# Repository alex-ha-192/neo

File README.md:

# Neo
 
The Neo buzzer system is an open-source, hopefully reliable, and hopefully affordable line of quiz lockout buzzers. It also does not currently exist. This is a rather significant flaw, though one I'm working to repair.

The initial planning is for one set of buzzers intended to have user-facing backwards compatibility with a popular set of commercial buzzers. A cheaper option may follow depending on how that goes.

## Progress

### Classic v1

- [x] Finalise design concepts
- [x] Source parts
- [ ] PCB design
- [ ] Order and initial testing
- [ ] 3D printed case design
- [ ] Real-world testing
- [ ] Release

## Pricing

I'm trying to be cost-conscious while designing these buzzers, but I'm not planning on imminently selling any or distributing them beyond Imperial until they're both finished and well-tested. If you need a buzzer set now, I'll point you to buying a [Kitsune system](https://github.com/Amekyras/kitsune) from [Aisling Skeet](https://github.com/Amekyras); they're a solid set of buzzers and they've been tested at quite a few competitive events. If you want a pricing estimate, it's probably whatever I say it is at the moment plus a bit on top because this keeps getting more expensive with every revision.

Just a quick note as well, this is an open-source project and, as a result, you can do whatever you'd like as per the [licence](LICENCE), but if you want to make your own buzzers, please don't sell them? Obviously I neither can nor will try and stop you, but these haven't been particularly cheap to work on, even though as I write this I haven't shipped out any PCBs yet - parts are expensive! I'd love it if anyone who wants to improve them does that though, either on this repository or on your own fork.

## Features (planned, WIP)

### Classic v1.0

- Daisy-chain as many buzzers per side as you could ever reasonably want
- USB-C connection with data for potential [BuzzIn.live](https://buzzin.live) support or generic input
- Low/fair latency
- Static discharge protection and industrial signalling for reliability
- At-home reflashable central unit firmware for customisation/DIY firmware upgrades
- Open source!

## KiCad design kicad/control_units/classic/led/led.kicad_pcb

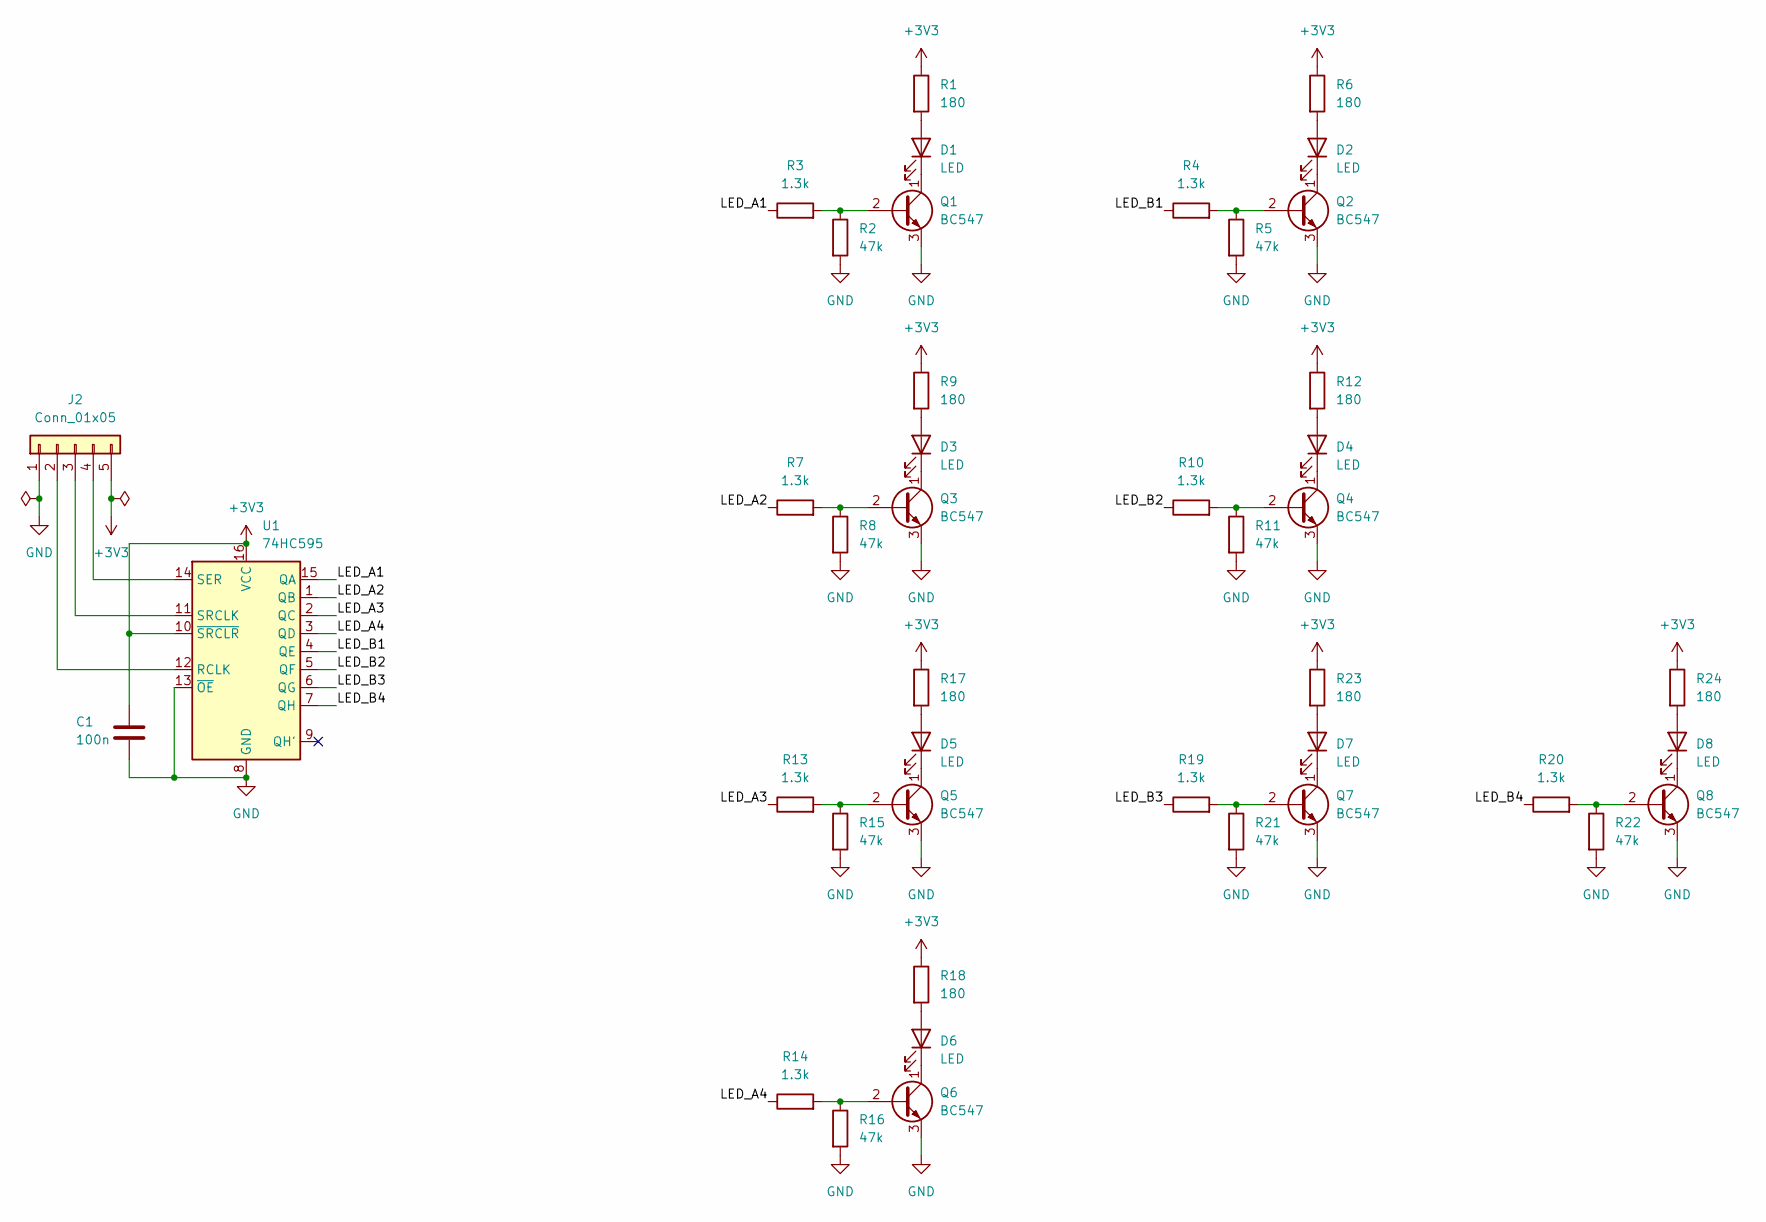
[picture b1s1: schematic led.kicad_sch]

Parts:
C1: 100n; C_Disc_D5.0mm_W2.5mm_P2.50mm
D1, D2, D3, D4, D5, D6, D7, D8: LED; LED_D5.0mm
J2: Conn_01x05; PinSocket_1x05_P2.54mm_Vertical
Q1, Q2, Q3, Q4, Q5, Q6, Q7, Q8: BC547; TO-92_Inline
R1, R6, R9, R12, R17, R18, R23, R24: 180; R_Axial_DIN0207_L6.3mm_D2.5mm_P7.62mm_Horizontal
R2, R5, R8, R11, R15, R16, R21, R22: 47k; R_Axial_DIN0207_L6.3mm_D2.5mm_P7.62mm_Horizontal
R3, R4, R7, R10, R13, R14, R19, R20: 1.3k; R_Axial_DIN0207_L6.3mm_D2.5mm_P7.62mm_Horizontal
U1: 74HC595; DIP-16_W7.62mm

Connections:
+3V3: C1.1, J2.5, R1.1, R6.1, R9.1, R12.1, R17.1, R18.1, R23.1, R24.1, U1.10 (~SRCLR), U1.16 (VCC)
/LED_A1: R3.1, U1.15 (QA)
/LED_A2: R7.1, U1.1 (QB)
/LED_A3: R13.1, U1.2 (QC)
/LED_A4: R14.1, U1.3 (QD)
/LED_B1: R4.1, U1.4 (QE)
/LED_B2: R10.1, U1.5 (QF)
/LED_B3: R19.1, U1.6 (QG)
/LED_B4: R20.1, U1.7 (QH)
GND: C1.2, J2.1, Q1.3 (E), Q2.3 (E), Q3.3 (E), Q4.3 (E), Q5.3 (E), Q6.3 (E), Q7.3 (E), Q8.3 (E), R2.2, R5.2, R8.2, R11.2, R15.2, R16.2, R21.2, R22.2, U1.8 (GND), U1.13 (~OE)
unnamed: D1.2 (A), R1.2
unnamed: D1.1 (K), Q1.1 (C)
unnamed: D2.2 (A), R6.2
unnamed: D2.1 (K), Q2.1 (C)
unnamed: D3.2 (A), R9.2
unnamed: D3.1 (K), Q3.1 (C)
unnamed: D4.2 (A), R12.2
unnamed: D4.1 (K), Q4.1 (C)
unnamed: D5.2 (A), R17.2
unnamed: D5.1 (K), Q5.1 (C)
unnamed: D6.2 (A), R18.2
unnamed: D6.1 (K), Q6.1 (C)
unnamed: D7.2 (A), R23.2
unnamed: D7.1 (K), Q7.1 (C)
unnamed: D8.2 (A), R24.2
unnamed: D8.1 (K), Q8.1 (C)
unnamed: J2.2, U1.12 (RCLK)
unnamed: J2.3, U1.11 (SRCLK)
unnamed: J2.4, U1.14 (SER)
unnamed: Q1.2 (B), R2.1, R3.2
unnamed: Q2.2 (B), R4.2, R5.1
unnamed: Q3.2 (B), R7.2, R8.1
unnamed: Q4.2 (B), R10.2, R11.1
unnamed: Q5.2 (B), R13.2, R15.1
unnamed: Q6.2 (B), R14.2, R16.1
unnamed: Q7.2 (B), R19.2, R21.1
unnamed: Q8.2 (B), R20.2, R22.1

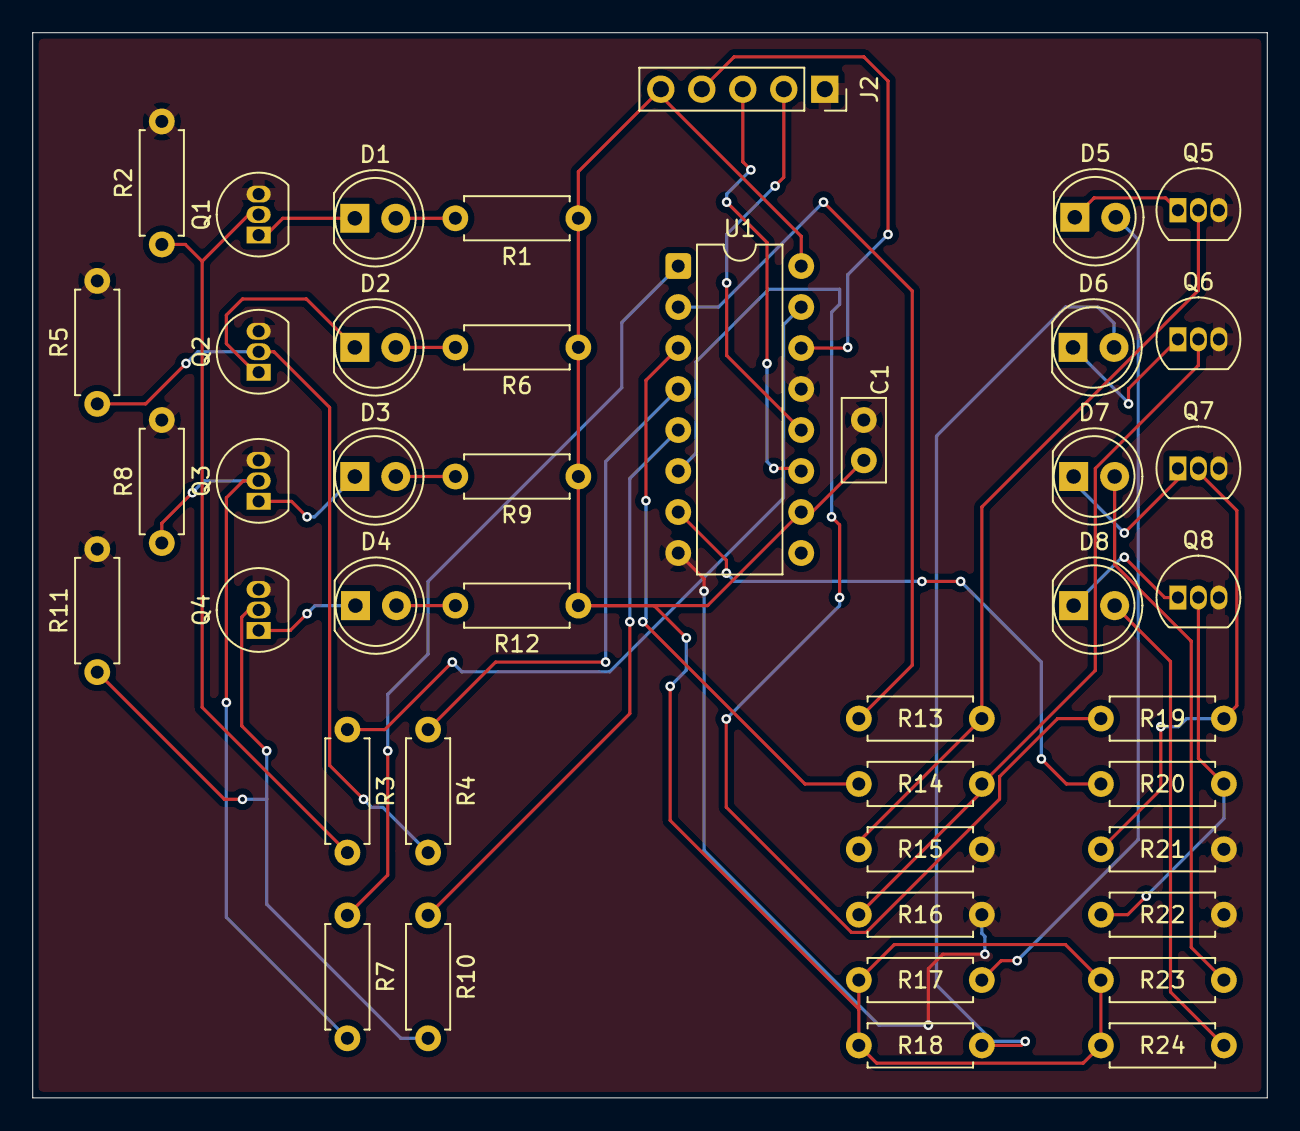
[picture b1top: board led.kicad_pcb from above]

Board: 2 copper layers, 76.5 x 66.0 mm, 43 parts (0 on the bottom side), 37 nets.

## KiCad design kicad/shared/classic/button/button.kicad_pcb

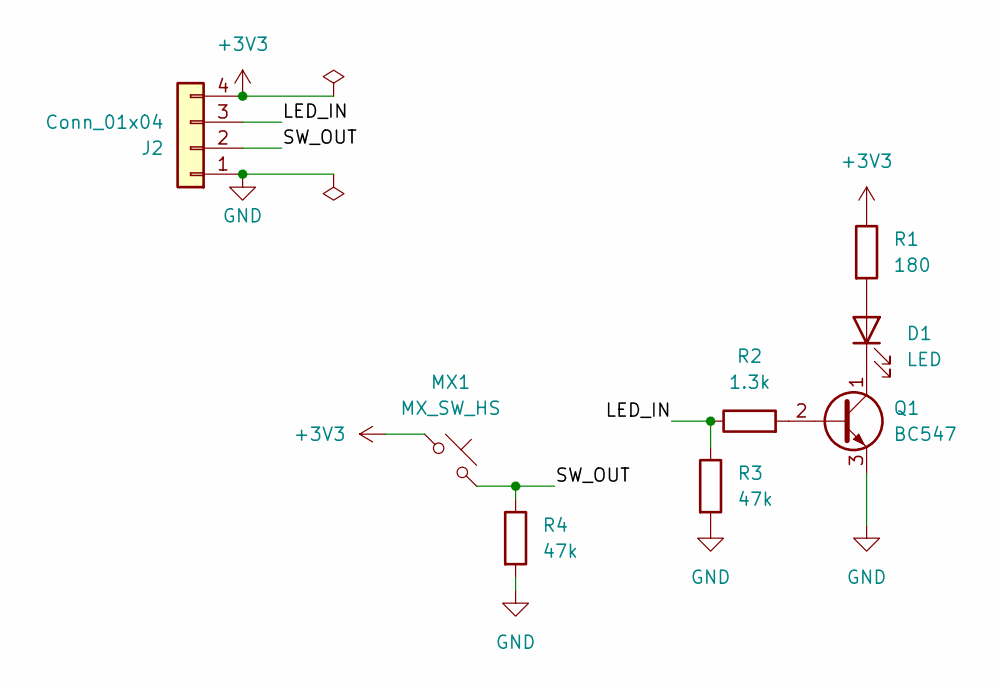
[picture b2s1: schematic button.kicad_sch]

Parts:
D1: LED; LED_D5.0mm
J2: Conn_01x04; PinSocket_1x04_P2.54mm_Vertical
MX1: MX_SW_HS; SW_MX_HS_CPG151101S11_1u
Q1: BC547; TO-92_Inline
R1: 180; R_Axial_DIN0207_L6.3mm_D2.5mm_P7.62mm_Horizontal
R2: 1.3k; R_Axial_DIN0207_L6.3mm_D2.5mm_P7.62mm_Horizontal
R3, R4: 47k; R_Axial_DIN0207_L6.3mm_D2.5mm_P7.62mm_Horizontal

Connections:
+3V3: J2.4, MX1.1, R1.1
/LED_IN: J2.3, R2.1, R3.1
/SW_OUT: J2.2, MX1.2, R4.1
GND: J2.1, Q1.3 (E), R3.2, R4.2
unnamed: D1.2 (A), R1.2
unnamed: D1.1 (K), Q1.1 (C)
unnamed: Q1.2 (B), R2.2

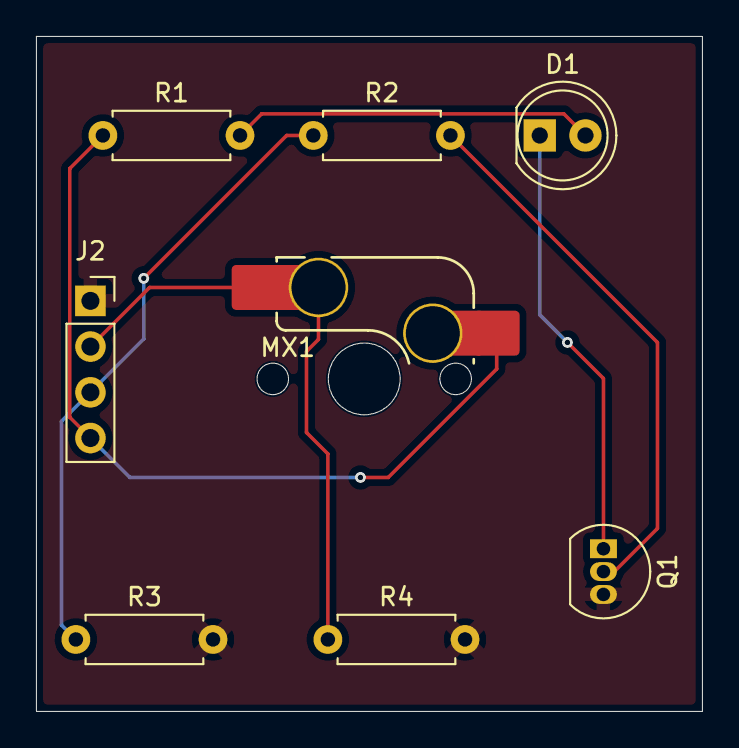
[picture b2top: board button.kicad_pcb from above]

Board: 2 copper layers, 37.0 x 37.5 mm, 8 parts (0 on the bottom side), 7 nets.

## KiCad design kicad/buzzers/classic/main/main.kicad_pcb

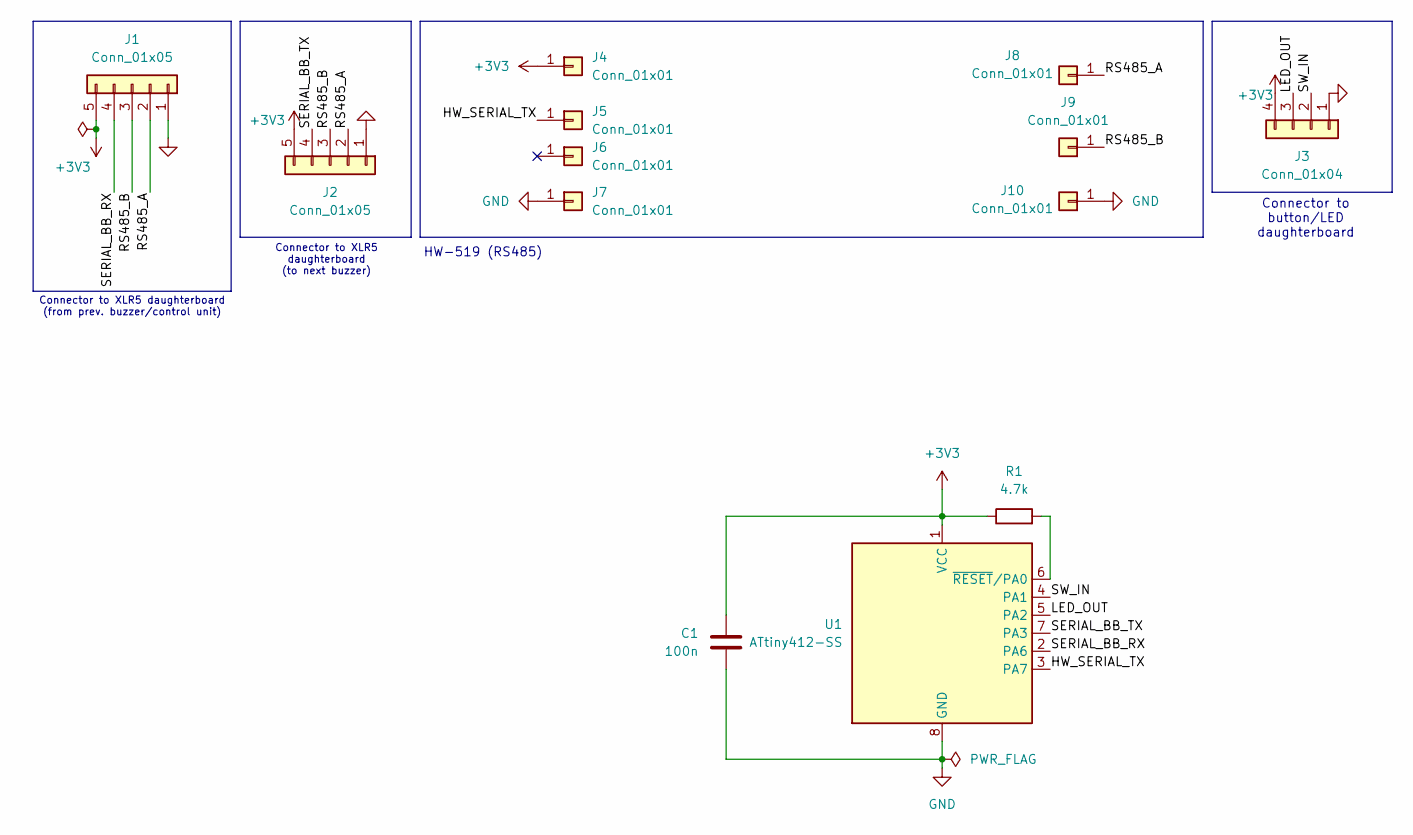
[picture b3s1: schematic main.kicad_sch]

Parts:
C1: 100n; C_Disc_D4.7mm_W2.5mm_P5.00mm
J1, J2: Conn_01x05; PinSocket_1x05_P2.54mm_Vertical
J3: Conn_01x04; PinSocket_1x04_P2.54mm_Vertical
J4, J5, J6, J7, J8, J9, J10: Conn_01x01; PinSocket_1x01_P2.54mm_Vertical
R1: 4.7k; R_Axial_DIN0207_L6.3mm_D2.5mm_P7.62mm_Horizontal
U1: ATtiny412-SS; SOIC-8_3.9x4.9mm_P1.27mm

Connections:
+3V3: C1.1, J1.5, J2.5, J3.4, J4.1 (Pin_1_1), R1.1, U1.1 (VCC)
/HW_SERIAL_TX: J5.1 (Pin_1_1), U1.3 (PA7)
/LED_OUT: J3.3, U1.5 (PA2)
/RS485_A: J1.2, J2.2, J8.1 (Pin_1_1)
/RS485_B: J1.3, J2.3, J9.1 (Pin_1_1)
/SERIAL_BB_RX: J1.4, U1.2 (PA6)
/SERIAL_BB_TX: J2.4, U1.7 (PA3)
/SW_IN: J3.2, U1.4 (PA1)
GND: C1.2, J1.1, J2.1, J3.1, J7.1 (Pin_1_1), J10.1 (Pin_1_1), U1.8 (GND)
unnamed: R1.2, U1.6 (~RESET/PA0)

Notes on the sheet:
Connector to button/LED daughterboard
HW-519 (RS485)
Connector to XLR5 daughterboard (from prev. buzzer/control unit)
Connector to XLR5 daughterboard (to next buzzer)

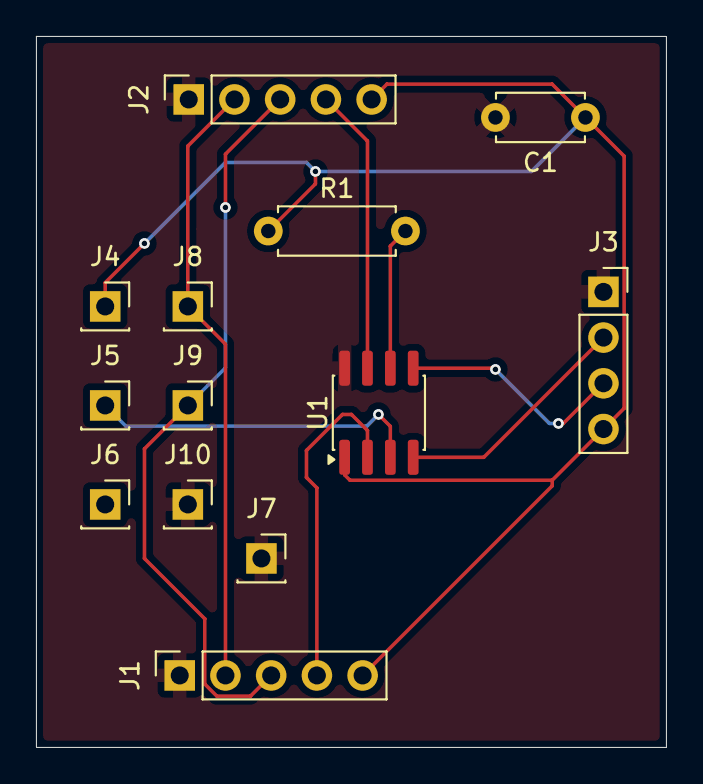
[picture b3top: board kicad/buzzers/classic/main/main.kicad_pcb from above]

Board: 2 copper layers, 35.0 x 39.5 mm, 13 parts (0 on the bottom side), 10 nets.

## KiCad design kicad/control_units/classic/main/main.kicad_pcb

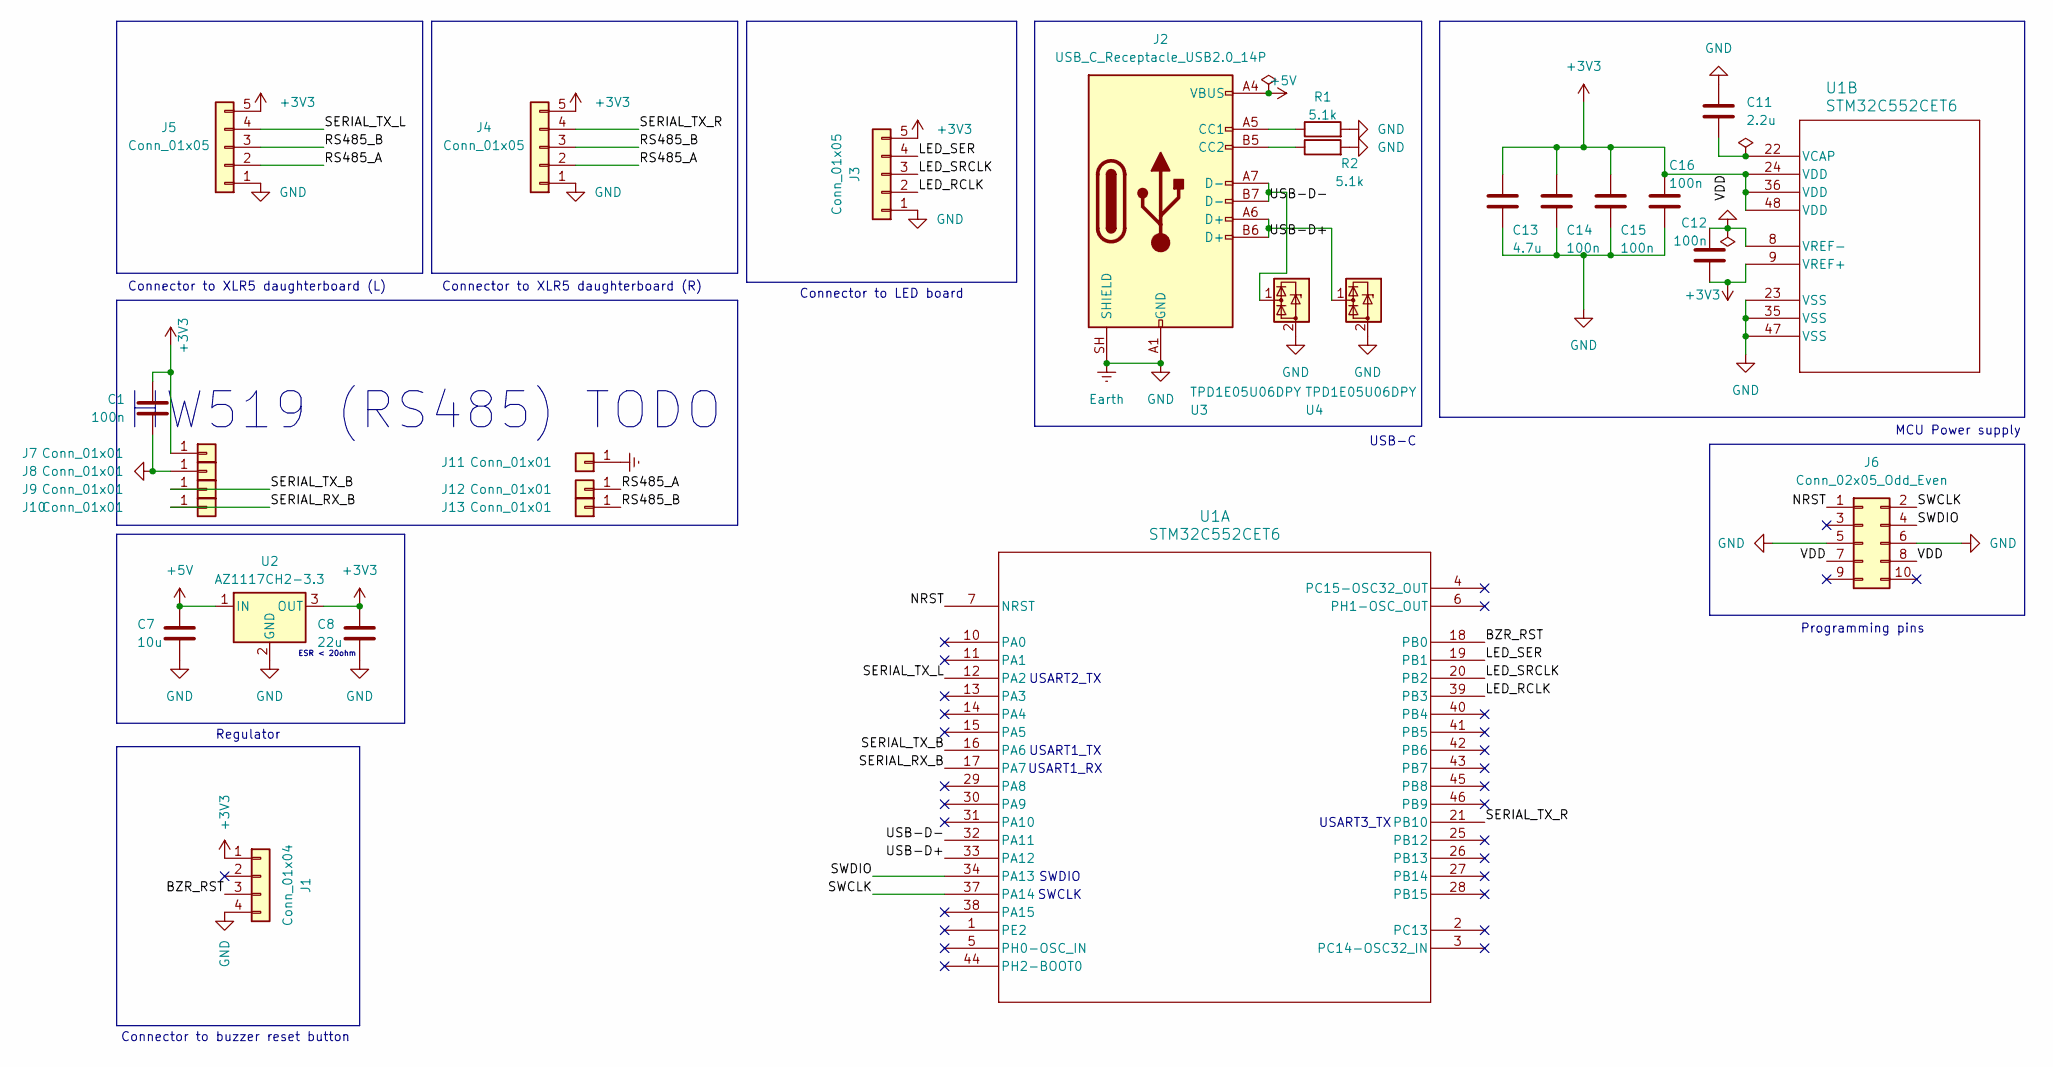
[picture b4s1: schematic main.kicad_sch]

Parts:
C1, C12, C14, C15, C16: 100n; C_Disc_D5.0mm_W2.5mm_P2.50mm
C7: 10u; CP_Radial_D5.0mm_P2.50mm
C8: 22u; CP_Radial_D5.0mm_P2.50mm
C11: 2.2u; C_Disc_D5.0mm_W2.5mm_P2.50mm
C13: 4.7u; C_Disc_D5.0mm_W2.5mm_P2.50mm
J1: Conn_01x04; PinSocket_1x04_P2.54mm_Vertical
J2: USB_C_Receptacle_USB2.0_14P; USB_C_Receptacle_Amphenol_12401610E4-2A
J3, J4, J5: Conn_01x05; PinSocket_1x05_P2.54mm_Vertical
J6: Conn_02x05_Odd_Even; PinSocket_2x05_P2.54mm_Vertical
J7, J8, J9, J10, J11, J12, J13: Conn_01x01; PinSocket_1x01_P2.54mm_Vertical
R1, R2: 5.1k; R_Axial_DIN0207_L6.3mm_D2.5mm_P7.62mm_Horizontal
U1: STM32C552CET6; LQFP-48_7x7mm_P0.5mm
U2: AZ1117CH2-3.3; SOT-223-3_TabPin2
U3, U4: TPD1E05U06DPY; Texas_DPY0002A_0.6x1mm_P0.65mm

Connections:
+3V3: C1.1, C8.2, C12.1, C13.2, C14.2, C15.2, C16.2, J1.1, J3.5, J4.5, J5.5, J6.7, J6.8, J7.1 (Pin_1_1), U1.9 (VREF+), U1.24 (VDD), U1.36 (VDD), U1.48 (VDD), U2.3 (OUT)
+5V: C7.2, J2.A4 (VBUS), J2.A9 (VBUS), J2.B4 (VBUS), J2.B9 (VBUS), U2.1 (IN)
/BZR_RST: J1.3, U1.18 (PB0)
/LED_RCLK: J3.2, U1.39 (PB3)
/LED_SER: J3.4, U1.19 (PB1)
/LED_SRCLK: J3.3, U1.20 (PB2)
/NRST: J6.1, U1.7 (NRST)
/RS485_A: J4.2, J5.2, J12.1 (Pin_1_1)
/RS485_B: J4.3, J5.3, J13.1 (Pin_1_1)
/SERIAL_RX_B: J10.1 (Pin_1_1), U1.17 (PA7)
/SERIAL_TX_B: J9.1 (Pin_1_1), U1.16 (PA6)
/SERIAL_TX_L: J5.4, U1.12 (PA2)
/SERIAL_TX_R: J4.4, U1.21 (PB10)
/SWCLK: J6.2, U1.37 (PA14)
/SWDIO: J6.4, U1.34 (PA13)
/USB-D+: J2.A6 (D+), J2.B6 (D+), U1.33 (PA12), U4.1 (I/O)
/USB-D-: J2.A7 (D-), J2.B7 (D-), U1.32 (PA11), U3.1 (I/O)
Earth: C1.2, C7.1, C8.1, C11.1, C12.2, C13.1, C14.1, C15.1, C16.1, J1.4, J2.A1 (GND), J2.A12 (GND), J2.B1 (GND), J2.B12 (GND), J2.SH (SHIELD), J3.1, J4.1, J5.1, J6.5, J6.6, J8.1 (Pin_1_1), J11.1 (Pin_1_1), R1.2, R2.2, U1.8 (VREF-), U1.23 (VSS), U1.35 (VSS), U1.47 (VSS), U2.2 (GND), U3.2 (GND), U4.2 (GND)
unnamed: J2.A5 (CC1), R1.1
unnamed: J2.B5 (CC2), R2.1
unnamed: C11.2, U1.22 (VCAP)

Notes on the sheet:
USB-C
Connector to XLR5 daughterboard (R)
Connector to buzzer reset button
ESR < 20ohm
USART2_TX
Regulator
USART1_TX
Programming pins
SWDIO
MCU Power supply
Connector to LED board
Connector to XLR5 daughterboard (L)
SWCLK
USART3_TX
USART1_RX
HW519 (RS485) TODO

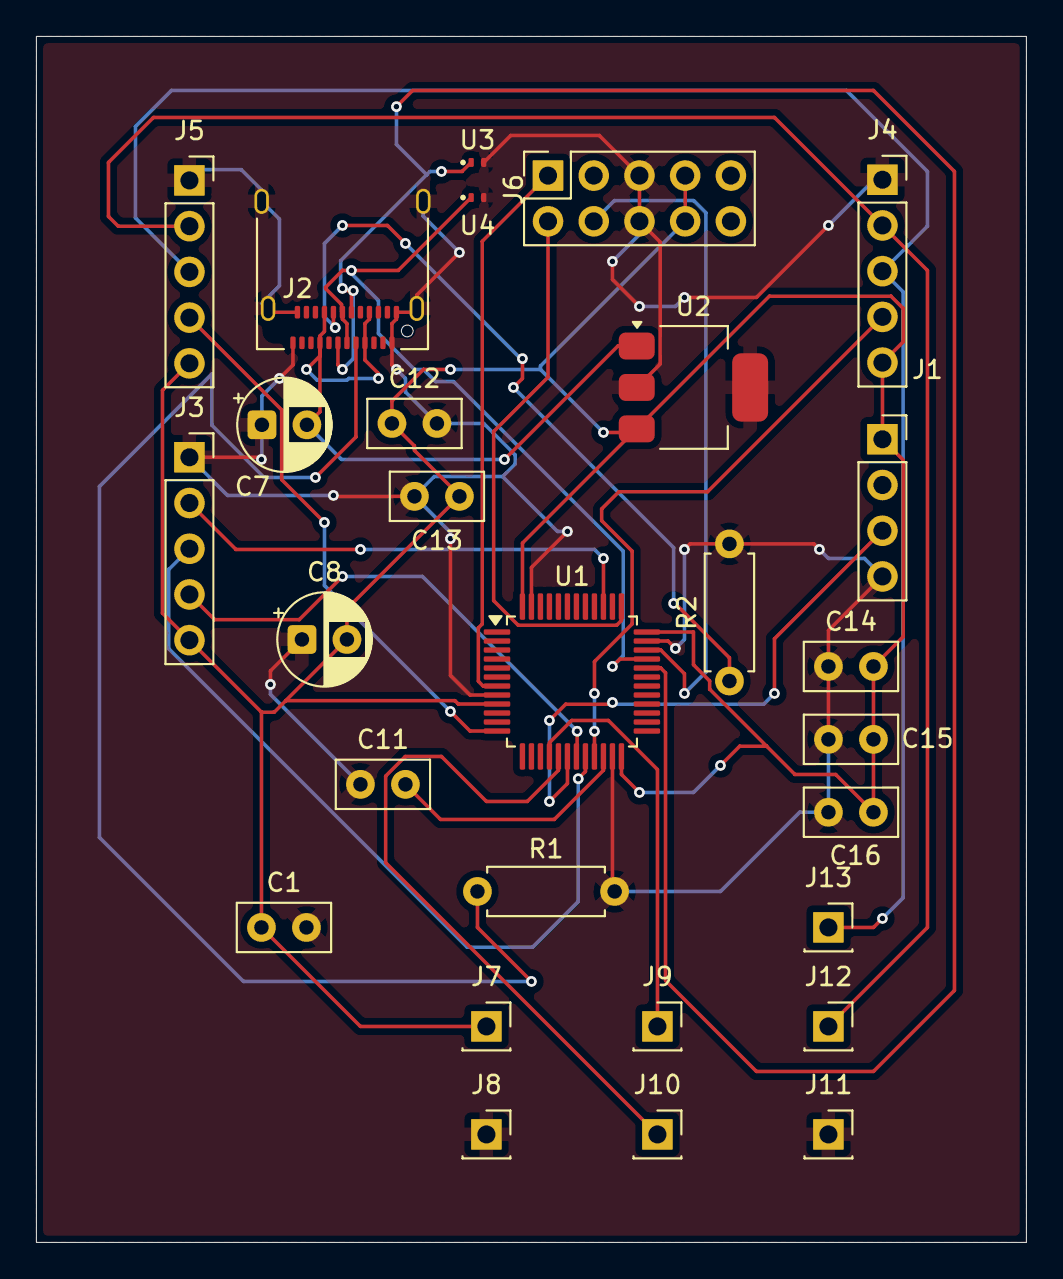
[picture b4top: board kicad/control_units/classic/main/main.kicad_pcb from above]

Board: 2 copper layers, 55.0 x 67.0 mm, 28 parts (0 on the bottom side), 21 nets.

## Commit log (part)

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2026-06-10 Added Obsidian vault for design notes
2026-06-10 added for Obsidian stuff
2026-06-10 Approximate BoM for really basic buzzers
2026-06-10 Need to check out GX12-4 at some point if it's cheaper than XLR4
2026-06-10 More BoM detail
2026-06-12 Refactor docs
2026-06-12 Added template KiCAD projects for all PCBs for Classic/Lite
2026-06-12 Add CERN Open Hardware Licence
    Added CERN Open Hardware Licence Version 2 - Strongly Reciprocal to the project.
2026-06-12 Enhance README with project overview and progress
    Added detailed project description and progress tracking.
2026-06-12 refactor pcb structure
2026-06-12 I make no guarantees
2026-06-12 Added keyboard switch parts
2026-06-12 Added male/female connector assembly PCB templates
2026-06-13 Yippee
2026-06-13 Draft of Classic button/LED assembly
2026-06-13 FW stuff
2026-06-13 Decoupling cap and JST-XA connector for Classic button daughterboard
2026-06-14 Pulldown for the switch bc I'm dumb
2026-06-14 feat: created LED board schematic for the Classic control unit (8 LEDs) using 74HC595 shift register, measurements needed for actual PCB
2026-06-15 Button/LED assembly Classic actually does the thing properly now
2026-06-16 Power supply for STM32 for Classic control unit
2026-06-16 More stuff for Classic control unit
2026-06-16 fix: Changed Classic control unit MCU and expanded schematic
2026-06-17 feat: Cleaned up pin arrangement for Classic button/LED assembly, added connector for that on Classic control unit main board, added pins for STM32 TODO
2026-06-17 fix: ESD earthing stuff etc. for HW-0519
2026-06-17 feat: Stuff for STM32 programming later
2026-06-17 Update README.md in a way that hopefully doesn't doxx me
2026-06-17 fix: Semi-colons are pretty cool actually
2026-06-17 feat: Added main Classic buzzer board; now basically just waiting on XLR5 and HW-0519 footprints; also need to see if I need a separate earth for the HW-0519s on the buzzer boards
2026-06-17 Update README.md
    I mean I don't have a HW-0519 yet, but it's basically there
2026-06-18 feat: Added connector schematics and fixed some other connectors in other schematics
2026-06-18 chore: Update README
2026-06-23 Added ESD protection for USB/RS485, not for serial lines yet; harmonised XLR pin numbers between boards
2026-06-23 Added some stuff for ESD protection on the serial lines; redid the STM32 programming pins
2026-06-27 feat: Should be able to footprint and route some prototype boards to see if I'm not totally off-base here
2026-06-27 feat: First revision of control unit main board; ignore the pad clearance violations, this shouldn't be an issue for the USB-C port specifically?
2026-06-27 chore: Fix README
2026-06-28 feat: Routed prototype THT component boards for buzzer and button/LED assembly PCBs
2026-06-29 feat: Should now be able to order some prototype PCBs to see if this whole thing actually works; note to self, buy some DIP sockets
